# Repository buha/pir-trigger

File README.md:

# pir-trigger
Camera trigger using PIR sensor

# Specifications
* 2.7" Eink screen
* PIR sensor
* Light sensor
* Camera focus and shutter control (any camera with 2.5mm native or adapted cable release)
* 5 way navigational buttons
* \>1 year on a 3V CR2477
* Weatherproof

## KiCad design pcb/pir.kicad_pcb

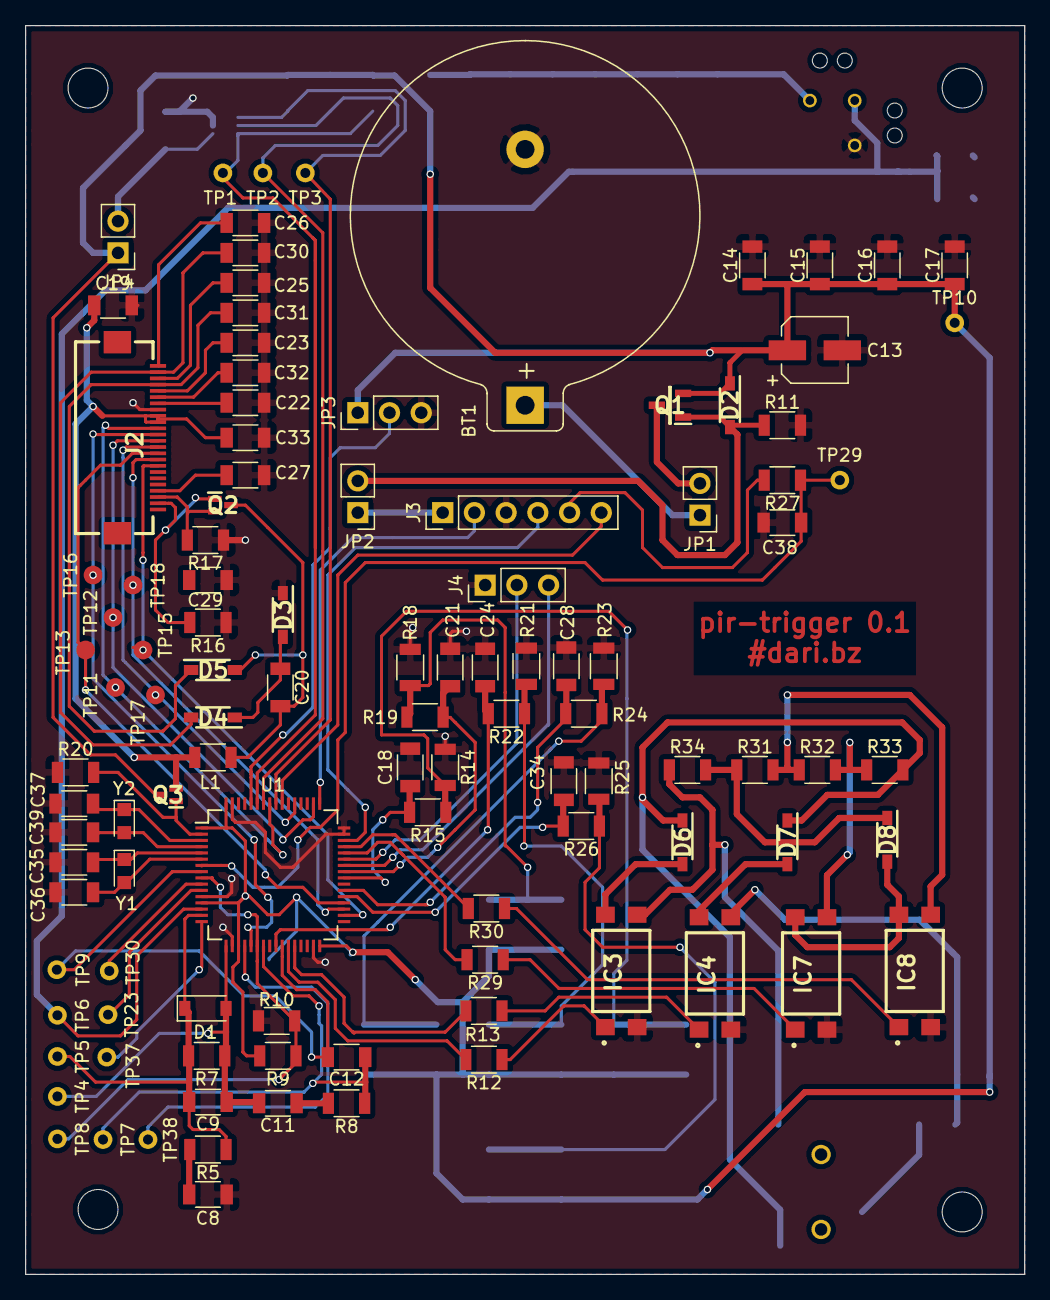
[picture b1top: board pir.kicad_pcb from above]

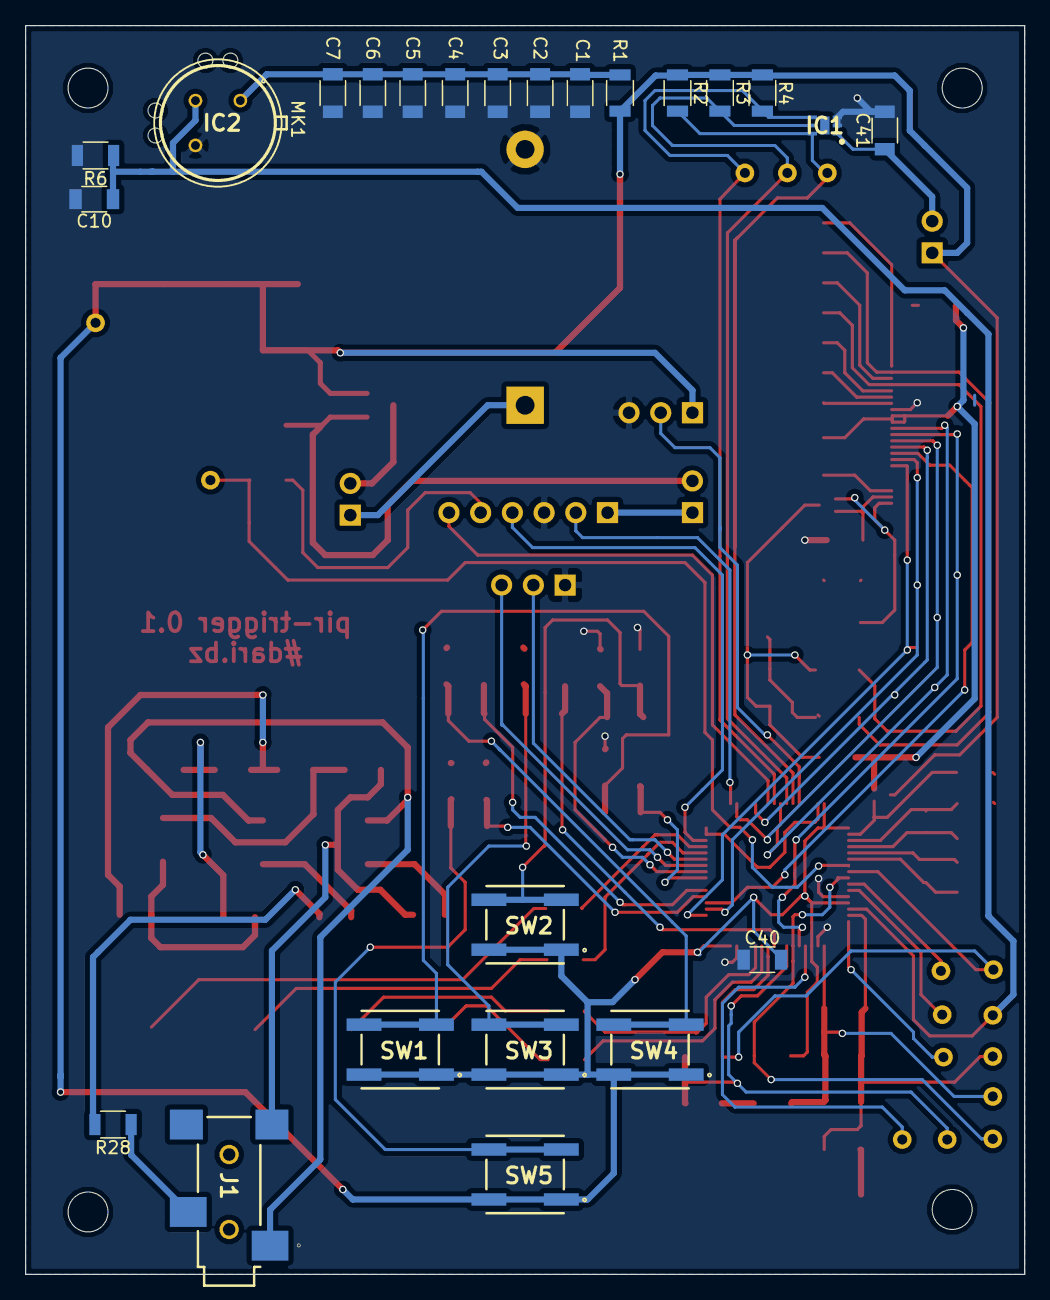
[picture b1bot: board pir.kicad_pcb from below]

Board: 2 copper layers, 80.0 x 100.0 mm, 133 parts (25 on the bottom side), 84 nets.

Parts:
BT1: CR2477 3V Battery; Keystone_105_1x2430-CoinCell
C1: 100μF; C_1206
C2, C14: 10μF; C_1206
C3, C15: 1μF; C_1206
C4, C16: 0.1μF; C_1206
C5, C17: 0.01μF; C_1206
C6: 1000pF; C_1206
C7: 100pF; C_1206
C8: 22μF; C_1206
C9, C12: 47nF; C_1206
C10: 3.3nF; C_1206
C11: 22uF; C_1206
C13: 100u; CP_Elec_5x5.3
C18, C21, C24, C28, C34, C38, C40: 100nF; C_1206
C19, C31: 4.7uF; C_1206
C20, C33: 100n; C_1206
C22, C23, C25, C26, C27, C29, C30, C32: 1uF; C_1206
C35, C36, C37, C39: 12pF; C_1206
C41: 0.1uF; C_1206
D1: 1N4148X-TP; D_SOD-123
D2, D3, D4, D5, D6, D7, D8: MBR0530; SOD3716X135N
IC1: MAX44009EDT+T; SON65P200X200X65-7N
IC2: IRA-S210ST01
IC3, IC4, IC7, IC8: EL817S
J1: SJ-2523-SMT-TR
J2: GDEW027W3; FH12A-24S-0.5SH
J3: SWD; Pin_Header_Straight_1x06_Pitch2.54mm
J4: UART; Pin_Header_Straight_1x03_Pitch2.54mm
JP1, JP2, JP4: Jumper; Pin_Header_Straight_1x02_Pitch2.54mm
JP3: Jumper_NC_Dual; Pin_Header_Straight_1x03_Pitch2.54mm
L1: 68uH; L_1206
MK1: IML-0688
Q1: SI2323DS; SOT95P237X112-3N
Q2, Q3: RE1C002UN; SOT50P160X85-3N
R1: 0; R_1206
R2, R3, R4, R15, R16, R19, R20, R22, R24, R26: 10k; R_1206
R5, R8: 13k; R_1206
R6: 56k; R_1206
R7: 680k; R_1206
R9, R10: 1M; R_1206
R11: 3.3K; R_1206
R12, R13, R28, R29, R30, R34: 150; R_1206
R14, R18, R21, R23, R25: 100k; R_1206
R17: 0.47; R_1206
R27: 1K; R_1206
R31: 36k; R_1206
R32: 2.9k; R_1206
R33: 2.2k; R_1206
SW1, SW2, SW3, SW4, SW5: SW_DPST-KSC931; KSC8(J)
TP1, TP2, TP3, TP4, TP5, TP6, TP7, TP8, TP9, TP10, TP23, TP29, TP30, TP37, TP38: TEST; Measurement_Point_Round-TH_Small
TP11, TP12, TP13, TP15, TP16, TP17, TP18: TEST; Measurement_Point_Round-SMD-Pad_Small
U1: STM32L476RETx; LQFP-64_10x10mm_Pitch0.5mm
Y1, Y2: 32 Mhz; Crystal_SMD_2012-2pin_2.0x1.2mm_HandSoldering

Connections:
/battery/Debugger3V3: J3.1, JP2.1
/camera/FOCUS: R12.2, U1.27
/camera/PANAFOCUS: R30.2, U1.45
/camera/PANASHUTTER: R29.2, U1.44
/camera/SHUTTER: R13.2, U1.28
/sensor/Ambient: IC1.4, R4.2, TP3.1, U1.56
/sensor/OPAMP1+: C10.1, IC2.2, R6.1, TP6.1, U1.14
/sensor/OPAMP1-: C9.2, D1.1, R5.1, R7.2, TP5.1, U1.15
/sensor/OPAMP1OUT: C9.1, C11.2, D1.2, R7.1, TP4.1, U1.17
/sensor/OPAMP2+: R9.1, R10.2, TP8.1, U1.9, U1.22
/sensor/OPAMP2-: C12.1, R8.1, TP7.1, U1.23
/sensor/OPAMP2OUT: C12.2, TP9.1, U1.8, U1.26
/sensor/SCL: IC1.5, R3.2, TP2.1, U1.58
/sensor/SDA: IC1.6, R2.2, TP1.1, U1.59
/soc/Down: C34.2, R26.2, U1.37
/soc/EINK_BS: J2.8, TP15.1, U1.34
/soc/EINK_BUSY: J2.9, TP18.1, U1.35
/soc/EINK_CS: J2.12, TP12.1, U1.50
/soc/EINK_D/C: J2.11, TP17.1, U1.53
/soc/EINK_MOSI: J2.14, TP11.1, U1.57
/soc/EINK_PWR: Q3.1, R20.2, U1.2
/soc/EINK_RST: J2.10, TP13.1, U1.36
/soc/EINK_SCK: J2.13, TP16.1, U1.21
/soc/Left: C18.2, R15.2, U1.40
/soc/OK: C24.2, R22.2, U1.25
/soc/Right: C28.2, R24.2, U1.38
/soc/Up: C21.2, R19.2, U1.41
/user/EINK_VCC: C19.1, C33.1, J2.15, J2.16, L1.1, Q3.2
/user/GDR: J2.2, Q2.1, R16.2
/user/PREVGH: C31.2, D5.1, J2.21
/user/PREVGL: C30.2, D4.2, J2.23
/user/RESE: J2.3, Q2.2, R17.2
Earth: BT1.2, C1.2, C2.2, C3.2, C4.2, C5.2, C6.2, C7.2, C8.2, C10.2, C13.2, C14.2, C15.2, C16.2, C17.2, C18.1, C19.2, C21.1, C22.1, C23.1, C24.1, C25.1, C26.2, C27.1, C28.1, C29.2, C30.1, C31.1, C32.1, C33.2, C34.1, C35.1, C36.1, C37.1, C38.1, C39.1, C40.1, C41.2, D3.1, IC1.2, IC1.3, IC2.3, IC3.2, IC4.2, IC7.2, IC8.2, J2.17, J3.3, J4.1, JP3.3, R6.2, R10.1, R11.2, R14.1, R16.1, R17.1, R18.1, R20.1, R21.1, R23.1, R25.1, U1.12, U1.18, U1.31, U1.47, U1.48, U1.63
unnamed: BT1.1, JP1.1
unnamed: C1.1, C2.1, C3.1, C4.1, C5.1, C6.1, C7.1, IC2.1, R1.1
unnamed: C8.1, R5.2
unnamed: C11.1, R8.2
unnamed: C20.1, D3.2, D4.1
unnamed: C20.2, D5.2, L1.2, Q2.3
unnamed: C22.2, J2.18
unnamed: C23.2, J2.20
unnamed: C25.2, J2.22
unnamed: C26.1, J2.24
unnamed: C27.2, J2.4
unnamed: C32.2, J2.19
unnamed: C35.2, U1.5, Y1.1
unnamed: C36.2, U1.6, Y1.2
unnamed: C37.2, U1.3, Y2.1
unnamed: C38.2, R27.1, TP29.1, U1.7
unnamed: C39.2, U1.4, Y2.2
unnamed: C41.1, IC1.1, JP4.2
unnamed: D2.2, JP2.2, Q1.1, R11.1
unnamed: D6.2, IC3.4
unnamed: D7.2, IC4.4
unnamed: D8.1, R31.1, R34.2
unnamed: D8.2, IC7.4, IC8.4
unnamed: IC3.1, R12.1
unnamed: IC4.1, R13.1
unnamed: IC4.3, R28.2
unnamed: IC7.1, R29.1
unnamed: IC7.3, R32.2, R33.1
unnamed: IC8.1, R30.1
unnamed: IC8.3, R31.2, R32.1
unnamed: JP1.2, Q1.3
unnamed: JP3.2, U1.60
unnamed: R14.2, R15.1, SW1.2, SW1.3
unnamed: R18.2, R19.1, SW2.2, SW2.3
unnamed: R21.2, R22.1, SW3.2, SW3.3
unnamed: R23.2, R24.1, SW4.2, SW4.3
unnamed: R25.2, R26.1, SW5.2, SW5.3
unnamed: TP23.1, U1.11
unnamed: TP30.1, U1.10
unnamed: TP37.1, U1.16
unnamed: TP38.1, U1.20
RING: IC3.3, J1.2, R34.1
RX: J4.2, U1.43
SHIELD: D6.1, D7.1, J1.1, R33.2
SWCLK: J3.2, U1.49
SWDIO: J3.4, U1.46
SWO: J3.6, U1.55
TIP: J1.3, R28.1
TX: J4.3, U1.42
VCC: C13.1, C14.1, C15.1, C16.1, C17.1, C40.2, D2.1, JP3.1, JP4.1, Q1.2, Q3.3, R1.2, R2.1, R3.1, R4.1, R9.2, SW1.1, SW1.4, SW2.1, SW2.4, SW3.1, SW3.4, SW4.1, SW4.4, SW5.1, SW5.4, TP10.1, U1.1, U1.13, U1.19, U1.32, U1.64
nRESET: J3.5, R27.2

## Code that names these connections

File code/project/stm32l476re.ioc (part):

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Mcu.Name=STM32L476R(C-E-G)Tx
Mcu.Package=LQFP64
Mcu.UserName=STM32L476RETx
PA0.GPIOParameters=GPIO_Label
PA0.GPIO_Label=OPAMP1+
PA0.Mode=Standalone
PA0.Signal=OPAMP1_VINP
PA1.GPIOParameters=GPIO_Label
PA1.GPIO_Label=OPAMP1-
PA1.Mode=Standalone
PA1.Signal=OPAMP1_VINM
PA10.Mode=Asynchronous
PA10.Signal=USART1_RX
PA11.GPIOParameters=GPIO_Label
PA11.GPIO_Label=PANASHUTTER
PA11.Signal=GPIO_Output
PA12.GPIOParameters=GPIO_Label
PA12.GPIO_Label=PANAFOCUS
PA12.Signal=GPIO_Output
PA13\ (JTMS-SWDIO).Mode=Trace_Asynchronous_SW
PA13\ (JTMS-SWDIO).Signal=SYS_JTMS-SWDIO
PA14\ (JTCK-SWCLK).Mode=Trace_Asynchronous_SW
PA14\ (JTCK-SWCLK).Signal=SYS_JTCK-SWCLK
PA15\ (JTDI).GPIOParameters=GPIO_Label
PA15\ (JTDI).GPIO_Label=CS
PA15\ (JTDI).Mode=NSS_Signal_Hard_Output
PA15\ (JTDI).Signal=SPI1_NSS
PA3.Mode=Standalone
PA3.Signal=OPAMP1_VOUT
PA5.GPIOParameters=GPIO_Label
PA5.GPIO_Label=SCK
PA5.Mode=TX_Only_Simplex_Unidirect_Master
PA5.Signal=SPI1_SCK
PA6.GPIOParameters=GPIO_Label
PA6.GPIO_Label=OPAMP2+
PA6.Mode=PGA Connected
PA6.Signal=OPAMP2_VINP
PA7.GPIOParameters=GPIO_Label
PA7.GPIO_Label=OPAMP2-
PA7.Mode=PGA Connected
PA7.Signal=OPAMP2_VINM
PA8.GPIOParameters=GPIO_Label
PA8.GPIO_Label=KEY_UP
PA8.Signal=GPXTI8
PA9.Mode=Asynchronous
PA9.Signal=USART1_TX
PB0.GPIOParameters=GPIO_Label
PB0.GPIO_Label=OPAMP2OUT
PB0.Mode=PGA Connected
PB0.Signal=OPAMP2_VOUT
PB1.GPIOParameters=GPIO_Label
PB1.GPIO_Label=FOCUS
PB1.Signal=GPIO_Output
PB13.GPIOParameters=GPIO_Label
PB13.GPIO_Label=EINK_BS
PB13.Signal=GPIO_Input
PB14.GPIOParameters=GPIO_Label
PB14.GPIO_Label=EINK_BUSY
PB14.Signal=GPIO_Input
PB15.GPIOParameters=GPIO_Label
PB15.GPIO_Label=EINK_RST
PB15.Signal=GPIO_Output
PB2.GPIOParameters=GPIO_Label
PB2.GPIO_Label=SHUTTER
PB2.Signal=GPIO_Output
PB3\ (JTDO-TRACESWO).Mode=Trace_Asynchronous_SW
PB3\ (JTDO-TRACESWO).Signal=SYS_JTDO-SWO
PB4\ (NJTRST).GPIOParameters=GPIO_Label
PB4\ (NJTRST).GPIO_Label=AMBIENT
PB4\ (NJTRST).Signal=GPXTI4
PB5.GPIOParameters=GPIO_Label
PB5.GPIO_Label=MOSI
PB5.Mode=TX_Only_Simplex_Unidirect_Master
PB5.Signal=SPI1_MOSI
PB6.GPIOParameters=GPIO_Label
PB6.GPIO_Label=SCL
PB6.Mode=I2C
PB6.Signal=I2C1_SCL
PB7.GPIOParameters=GPIO_Label
PB7.GPIO_Label=SDA
PB7.Mode=I2C
PB7.Signal=I2C1_SDA
PC0.GPIOParameters=GPIO_Label
PC0.GPIO_Label=OPAMP2OUT
PC0.Signal=ADCx_IN1
PC1.GPIOParameters=GPIO_Label
PC1.GPIO_Label=OPAMP2+
PC1.Signal=ADCx_IN2
PC12.GPIOParameters=GPIO_Label
PC12.GPIO_Label=EINK_DC
PC12.Signal=GPIO_Input
PC13.GPIOParameters=GPIO_Label
PC13.GPIO_Label=EINK_PWR
PC13.Signal=GPIO_Output
PC14-OSC32_IN\ (PC14).Mode=LSE-External-Oscillator
PC14-OSC32_IN\ (PC14).Signal=RCC_OSC32_IN
PC15-OSC32_OUT\ (PC15).Mode=LSE-External-Oscillator
PC15-OSC32_OUT\ (PC15).Signal=RCC_OSC32_OUT
PC5.GPIOParameters=GPIO_Label
PC5.GPIO_Label=KEY_OK
PC5.Signal=GPXTI5
PC6.GPIOParameters=GPIO_Label
PC6.GPIO_Label=KEY_DOWN
PC6.Signal=GPXTI6
PC7.GPIOParameters=GPIO_Label
PC7.GPIO_Label=KEY_RIGHT
PC7.Signal=GPXTI7
PC9.GPIOParameters=GPIO_Label
PC9.GPIO_Label=KEY_LEFT
PC9.Signal=GPXTI9
RCC.HSE_VALUE=8000000
board=hal

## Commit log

2018-02-03 KiCad project files and some components
    At this point it is not certain if I go with CC2540. EFR SoCs maybe?
2018-02-03 Fixed some absolute paths
2018-02-03 Library rework
2018-02-03 Library rework - 2
2018-02-03 Replaced CC2540F256RHAT with CC2541F128RHAT
    CC2540F256RHAT has a useless USB interface.
    CC2541F128RHAT has better radio power consumption and reduced flash,
    I don't need 256KB. Fingers crossed for some samples from TI.
    EFR32 Blue Gecko was the best alternative so far but I opted for TI
    because of its free CCS (versus IAR) environment. EFR32 has better
    radio power consumption than TI chips but worse standby current
2018-02-03 Added debugger interface
2018-02-03 User pushbutton
2018-02-03 Added some documentation + TODO's
2018-02-04 Added light sensor with IIC interface
2018-02-04 Migrated project/libraries to KiCad nightly build
    Revision: 821668d96
    Reason being the simulator feature and the better library management.
2018-02-04 Added simulation for the battery/debugger switch
2018-02-04 Battery/debugger switch implemented
2018-02-04 Simulation stage 1
2018-02-04 Stage 1 works with qucsator & ngspice
2018-02-04 Stage 2 simulation implemented
2018-02-05 Added stage 3 to simulator
2018-02-05 Added simulation for the alternative comparator
2018-02-05 Simulation source improvement
2018-02-05 Forgot C2/R2 in simulation
2018-02-09 LTSpice files for TI/ST designs
2018-02-09 Added Qucs simulation for ST design
2018-02-09 Added digitized sensor output from ST AN
    The conclusion of all these simulations is that the stage1
    feedback resistor must be digitally configurable.
    Needs some care because changing that resistor actually
    changes the filter response and we want to filter out
    anything beyond ~0.5Hz-5Hz.
2018-02-09 TODO update
2018-02-09 Reworked doc folder
2018-02-09 Added E-Ink display
2018-02-10 Added hierarchical signals for E-Ink
2018-02-10 Reverted to KiCad 4.0.7
    + Reworked debouncing for pushbuttons
2018-02-10 MCU change, again
    STM32L0 had quite a big problem, common reference for the comparators.
    Another minus was the missing SWO for debugging.
    STM32L4 has floating point, and most importantly, has embedded OPAMPS!
    This means I can directly plug in the filter to the analog inputs and
    everything is software. 2 opamps and 2 comparators (if needed).
    External circuitry would be minimal for the PIR sensor.
2018-02-10 Sensor logic implemented using MCU opamps
    Of the ST PIR design I use the first 2 stages only, so no comparators.
    1st stage using OPAMP1
    2nd stage using OPAMP2
    OPAMP1 amplifies the sensor output around the DC component of the PIR
    sensor.
    OPAMP2 amplifies the stage 1 output around half of VCC.
2018-02-11 Readded pir-cache.lib, deleting it fucked up .sch
2018-02-11 Reworked the front diagram
2018-02-11 Renamed all components
2018-02-11 Changed camera interface to use optocouplers
2018-02-11 Replaced original PIR symbol and ran ERC tests
2018-02-13 Added testpoints
2018-02-13 CvPcb crashes every time on launch
    This commit saves work just before trying out nightly kicad-git.
2018-02-13 Assigned footprints to all components
2018-02-13 Put the first components on layout
2018-02-13 I think I found a way to have Panasonic interface
    Uses 2 more optocouplers, 3 more diodes and some current limiting
    resistors.
2018-02-14 Reassigned some footprints, added some libraries
    Normally I can start working on PCB.
2018-02-19 Fixed board dimensions
2018-02-19 Started placing some components, finally
2018-02-20 More work on the PCB
    The opamp circuit is done.
    Currently working on camera interface.
    TODO: screen, buttons.
2018-02-20 Camera interface placement done.
2018-02-20 Finished the display components placement.
2018-02-20 Placed all components
    Still some routing to do though, and many TP's are not placed.
2018-02-21 Very few routes remaining
    Many TP's will be removed due to lack of space.
2018-02-22 Routed what seem to be the last useful tracks
2018-02-22 OK button MOVED TO A WKUP pin. PCB routing done.
    DRC passed.
    Unconnected tracks : 0.
2018-02-22 1 mounting hole was missing for some reason
2018-02-22 Changed buttons from Panasonic to C&K
2018-02-22 Gerber files for v0.1
    Not tagging yet, need to check some things
2018-02-22 Readme update
2018-02-23 Changed FPC display connector
    Same model from Hirose but Top-connect not Bottom-connect as it
    previously was. Huge mistake, got it in time.
    Created GDEW027W3 schematic symbol for the display.
2018-02-23 Regenerated gerbers after latest modifications
2018-03-05 v0.1 Prototype files sent to PCBWay
2018-03-07 STM32Cube file
    Partial.
2018-03-07 Kind of finished the STM32Cube project
2018-03-07 Generated skeleton project from STM32CubeMX
    I'm more inclined to go with a bare Makefile instead of IDE plugins nonsense.
    The Makefile had many errors though but I managed to make arm-none-eabi-gcc
    compile/link the project.
2018-03-10 Renamed code->firmware
2018-03-10 KEY_OK is now SYS_WKUP5, timebase changed to TIM1
    Regenerated all code. As in this commit, the code can be regene-
    rated using the hal.ioc file loaded up in STM32CubeMX.
    This will add additional files, or modify existing ones. I need
    to make sure to put code under USER CODE and not otherwise.
    Makefile is heavily reworked due to bugs in CubeMX generation so
    that one has to be manually merged.
2018-03-10 Added Code::Blocks project
2018-03-10 Debugger - arm-none-eabi-gdb + openocd
    Tested, works under Code::Blocks and cli.
    C::B needs `make debug` executed in a separate terminal.
    Working on improving this to automate the shutdown of
    openocd on debugger detach.
2018-03-11 Some changes to C::B prj file
    May change to Eclipse due to C::B issues:
    - doesn't properly parse preprocessor directives to grey out inactive code parts
    - no easy way to hard reset target device
    - starting freertos scheduler brings me back to main (might not be related to C::B)
2018-03-11 Watchdog was messing C::B debugger
    fixed.
2018-03-11 Added Eclipse (Atollic TrueSTUDIO) project files
    As for C::B, project is just a dumb project calling my Makefile.
    However, TrueSTUDIO has all the openocd, freertos, stm ... plugins
    which makes it more suitable.
    C::B debugger script changed to reset the target and continue to
    main on startup.
2018-03-11 Fuck eclipse workspace philosophy!!!
    Nevermind.
2018-03-12 Some temporary work in camera interface
    Shutter fires on my Nikon D600 but focus doesn't .. focus. It does
    something on camera, but it doesn't focus the lens at least.
2018-03-13 Polishing of the camera interface + settings
    Camera interface settings are stored in the *settings* module and
    all that goes into/out of it gets through some functions. For now
    the functions are basic but semaphores will be added later.
    This commit also adds intervalometer style parameters to the
    trigger settings and can now accomodate for all sort of inter-delays
    in-between and repetition of triggers.
2018-03-15 Addded & tested EXTI interrupts for buttons
    OK doesnt show up, maybe some soldering issue, will fix that.
2018-03-16 Excluded some CMSIS unused device headers
    Indexer was going crazy by showing too many results on F3.
2018-03-16 KEY_OK is now producing interrupts
    In cubemx I have configured it as SYS_WKUP (which is true) but this
    cubemx then removed it from the list of pins that should generate
    EXTI.
2018-03-16 Implemented input -> core ipc queue
    I can now pass info about what key was pressed between the tInput
    and tCore tasks.
    On problem I encountered was the fact that FreeRTOS blocks the
    usage of some of its ISR API if the NVIC Priority is above a certain
    threshold. In my case the threshold is 5 so I just modified the
    priority of the EXTI interrupt to 5 to allow that API subset to
2018-03-22 Refactored messed up OPAMPx+ OPAMPx- signals
2018-03-27 Work in ADC + created sensor task
    No results yet because fSensor is not executed.
2018-03-28 Increased heap size for FreeRTOS
    It failed to create its IDLE task, this is why I had issues executing
    the new fSensor task.
2018-03-28 Added DMA configuration for ADC
    DMA interrupts don't fire, something is still wrong.
